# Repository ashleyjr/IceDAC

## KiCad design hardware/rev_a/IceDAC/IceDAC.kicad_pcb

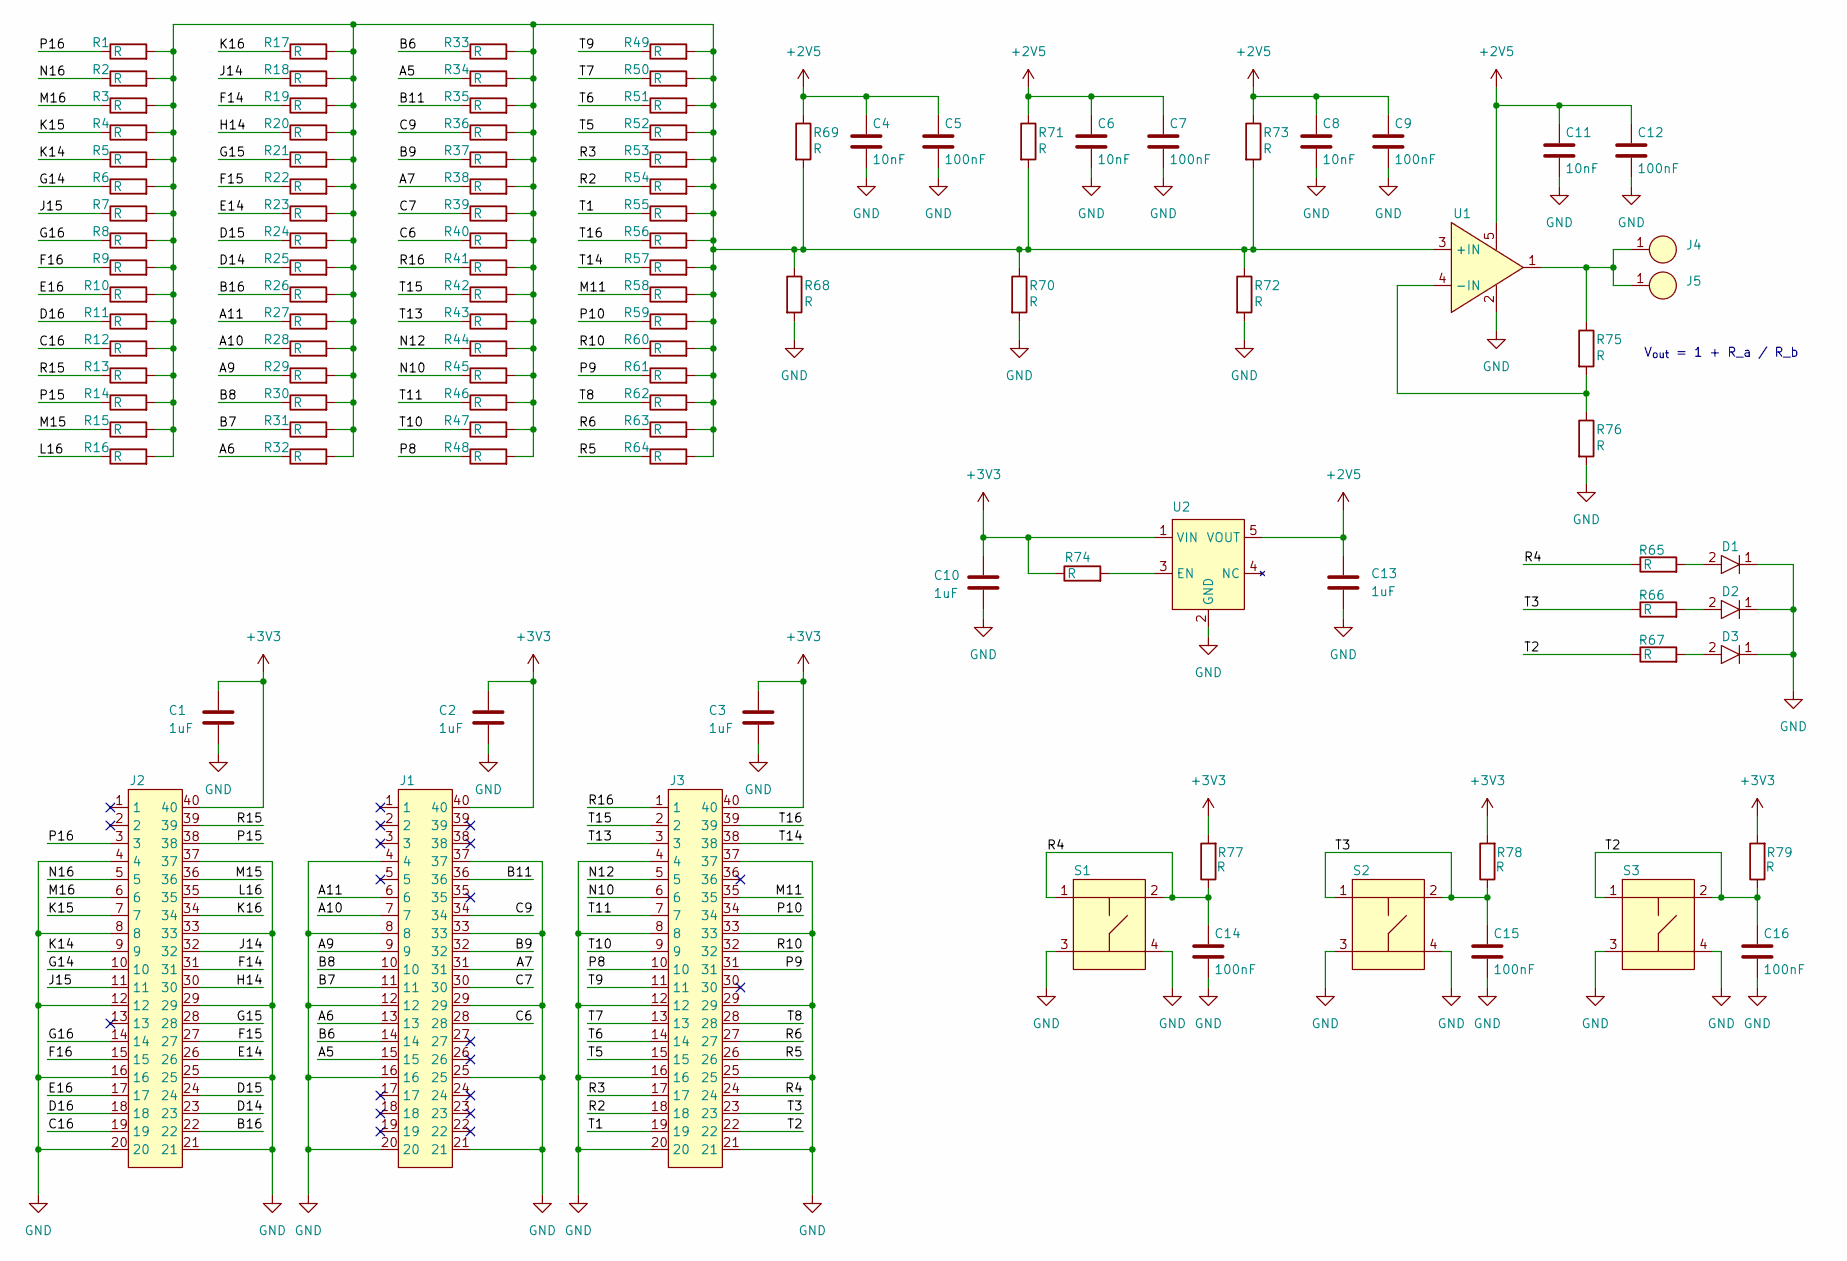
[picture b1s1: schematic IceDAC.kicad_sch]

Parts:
C1, C2, C3, C10, C13: 1uF; C_0603_1608Metric_Pad1.08x0.95mm_HandSolder
C4, C6, C8, C11: 10nF; C_0603_1608Metric_Pad1.08x0.95mm_HandSolder
C5, C7, C9, C12, C14, C15, C16: 100nF; C_0603_1608Metric_Pad1.08x0.95mm_HandSolder
D1, D2, D3: 150060GS75000
J1, J2, J3: M20-8761046
J4, J5: OUT
R1, R2, R3, R4, R5, R6, R7, R8, R9, R10, R11, R12, R13, R14, R15, R16, R17, R18, R19, R20, R21, R22, R23, R24, R25, R26, R27, R28, R29, R30, R31, R32, R33, R34, R35, R36, R37, R38, R39, R40, R41, R42, R43, R44, R45, R46, R47, R48, R49, R50, R51, R52, R53, R54, R55, R56, R57, R58, R59, R60, R61, R62, R63, R64, R65, R66, R67, R68, R69, R70, R71, R72, R73, R74, R75, R76, R77, R78, R79: R; R_0603_1608Metric_Pad0.98x0.95mm_HandSolder
S1, S2, S3: 1301.9315
U1: OPA354AIDBVR
U2: AP2112K-2.5TRG1

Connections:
+2V5: C4.1, C5.1, C6.1, C7.1, C8.1, C9.1, C11.1, C12.1, C13.1, R69.1, R71.1, R73.1, U1.5, U2.5 (VOUT)
+3V3: C1.1, C2.1, C3.1, C10.1, J1.40, J2.40, J3.40, R74.1, R77.2, R78.2, R79.2, U2.1 (VIN)
/A5: J1.15, R34.1
/A6: J1.13, R32.1
/A7: J1.31, R38.1
/A9: J1.9, R29.1
/A10: J1.7, R28.1
/A11: J1.6, R27.1
/B6: J1.14, R33.1
/B7: J1.11, R31.1
/B8: J1.10, R30.1
/B9: J1.32, R37.1
/B11: J1.36, R35.1
/B16: J2.22, R26.1
/C6: J1.28, R40.1
/C7: J1.30, R39.1
/C9: J1.34, R36.1
/C16: J2.19, R12.1
/D14: J2.23, R25.1
/D15: J2.24, R24.1
/D16: J2.18, R11.1
/E14: J2.26, R23.1
/E16: J2.17, R10.1
/F14: J2.31, R19.1
/F15: J2.27, R22.1
/F16: J2.15, R9.1
/G14: J2.10, R6.1
/G15: J2.28, R21.1
/G16: J2.14, R8.1
/H14: J2.30, R20.1
/J14: J2.32, R18.1
/J15: J2.11, R7.1
/K14: J2.9, R5.1
/K15: J2.7, R4.1
/K16: J2.34, R17.1
/L16: J2.35, R16.1
/M11: J3.35, R58.1
/M15: J2.36, R15.1
/M16: J2.6, R3.1
/N10: J3.6, R45.1
/N12: J3.5, R44.1
/N16: J2.5, R2.1
/P8: J3.10, R48.1
/P9: J3.31, R61.1
/P10: J3.34, R59.1
/P15: J2.38, R14.1
/P16: J2.3, R1.1
/R2: J3.18, R54.1
/R3: J3.17, R53.1
/R4: C14.1, J3.24, R65.1, R77.1, S1.1, S1.2
/R5: J3.26, R64.1
/R6: J3.27, R63.1
/R10: J3.32, R60.1
/R15: J2.39, R13.1
/R16: J3.1, R41.1
/T1: J3.19, R55.1
/T2: C16.1, J3.22, R67.1, R79.1, S3.1, S3.2
/T3: C15.1, J3.23, R66.1, R78.1, S2.1, S2.2
/T5: J3.15, R52.1
/T6: J3.14, R51.1
/T7: J3.13, R50.1
/T8: J3.28, R62.1
/T9: J3.11, R49.1
/T10: J3.9, R47.1
/T11: J3.7, R46.1
/T13: J3.3, R43.1
/T14: J3.38, R57.1
/T15: J3.2, R42.1
/T16: J3.39, R56.1
GND: C1.2, C2.2, C3.2, C4.2, C5.2, C6.2, C7.2, C8.2, C9.2, C10.2, C11.2, C12.2, C13.2, C14.2, C15.2, C16.2, D1.1, D2.1, D3.1, J1.4, J1.8, J1.12, J1.16, J1.20, J1.21, J1.25, J1.29, J1.33, J1.37, J2.4, J2.8, J2.12, J2.16, J2.20, J2.21, J2.25, J2.29, J2.33, J2.37, J3.4, J3.8, J3.12, J3.16, J3.20, J3.21, J3.25, J3.29, J3.33, J3.37, R68.2, R70.2, R72.2, R76.2, S1.3, S1.4, S2.3, S2.4, S3.3, S3.4, U1.2, U2.2 (GND)
unnamed: D1.2, R65.2
unnamed: D2.2, R66.2
unnamed: D3.2, R67.2
unnamed: J4.1, J5.1, R75.1, U1.1
unnamed: R1.2, R2.2, R3.2, R4.2, R5.2, R6.2, R7.2, R8.2, R9.2, R10.2, R11.2, R12.2, R13.2, R14.2, R15.2, R16.2, R17.2, R18.2, R19.2, R20.2, R21.2, R22.2, R23.2, R24.2, R25.2, R26.2, R27.2, R28.2, R29.2, R30.2, R31.2, R32.2, R33.2, R34.2, R35.2, R36.2, R37.2, R38.2, R39.2, R40.2, R41.2, R42.2, R43.2, R44.2, R45.2, R46.2, R47.2, R48.2, R49.2, R50.2, R51.2, R52.2, R53.2, R54.2, R55.2, R56.2, R57.2, R58.2, R59.2, R60.2, R61.2, R62.2, R63.2, R64.2, R68.1, R69.2, R70.1, R71.2, R72.1, R73.2, U1.3 (+IN)
unnamed: R75.2, R76.1, U1.4 (-IN)
unnamed: R74.2, U2.3 (EN)

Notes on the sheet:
V_{out} = 1 + R_a / R_b

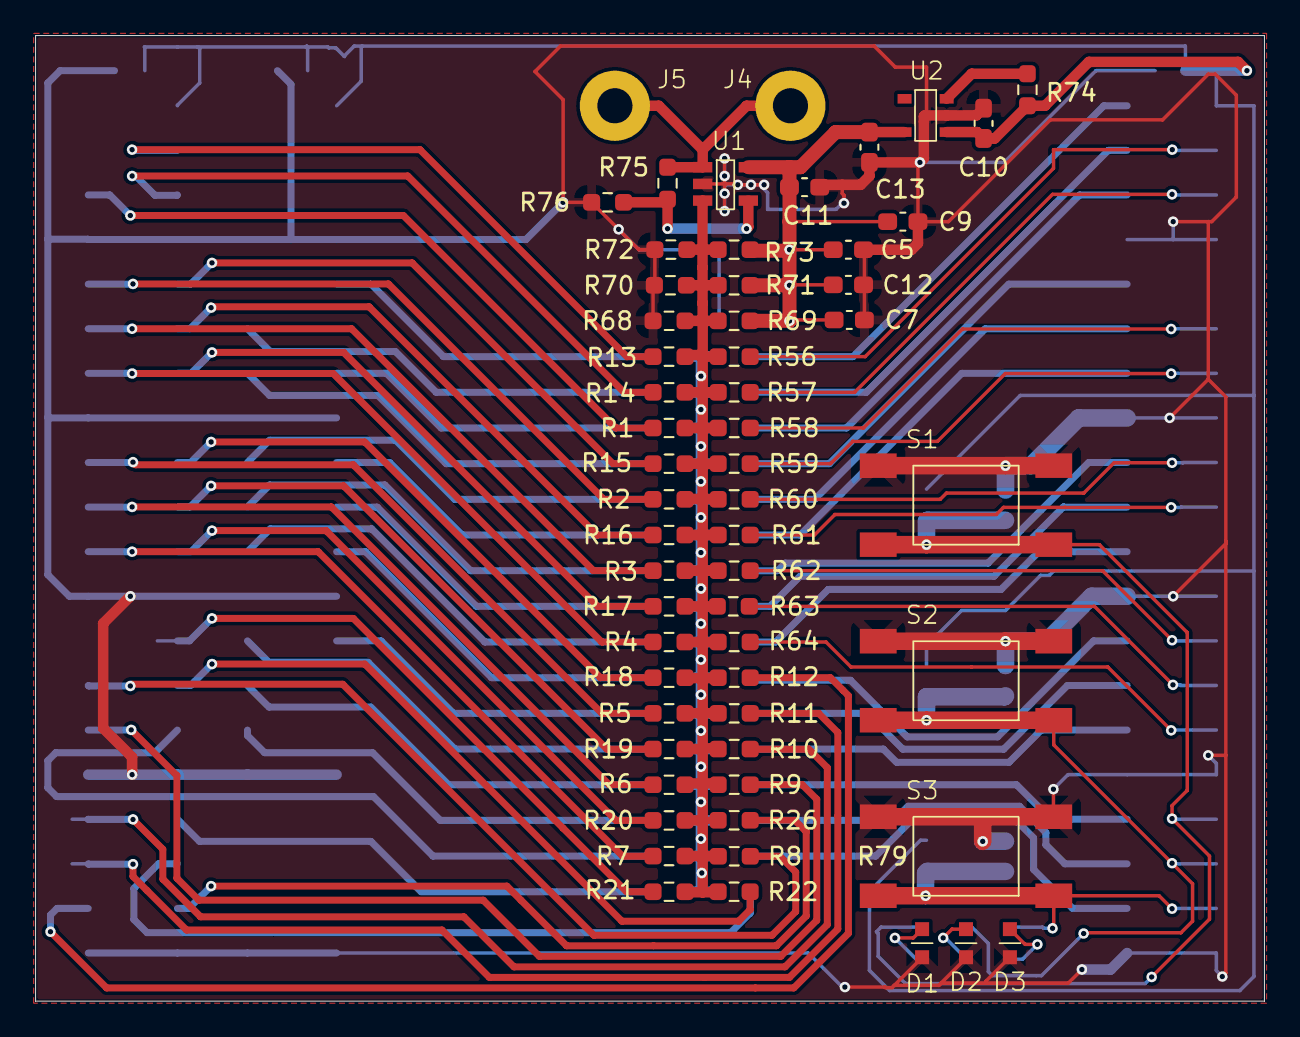
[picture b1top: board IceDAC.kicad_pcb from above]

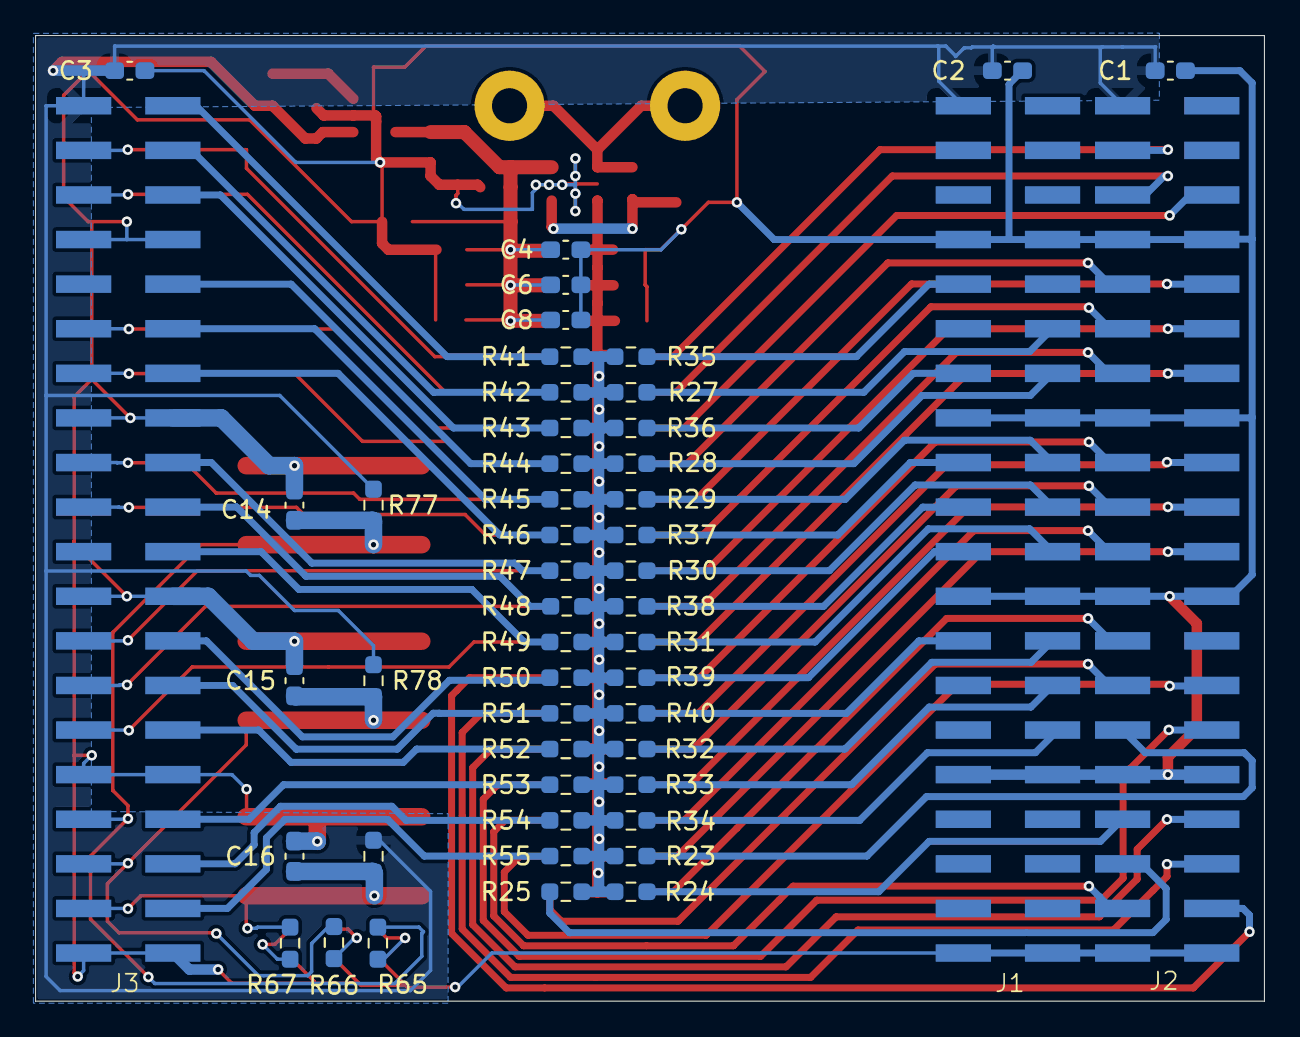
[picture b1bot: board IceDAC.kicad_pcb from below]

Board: 2 copper layers, 70.0 x 55.0 mm, 108 parts (47 on the bottom side), 77 nets.

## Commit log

2024-06-27 RTL and test
2024-06-27 sims
2024-06-27 add test bash
2024-06-27 x_mem
2024-06-27 x_mem sims
2024-06-27 first controller tests
2024-06-27 start top level
2024-06-27 add uart submodule
2024-06-27 build top
2024-06-27 synth
2024-06-27 reset
2024-06-28 UART test
2024-06-28 fpga working
2024-06-28 ram test
2024-07-02 tidy tb
2024-07-02 rsp test
2024-07-03 added gen script
2024-07-18 rev a
